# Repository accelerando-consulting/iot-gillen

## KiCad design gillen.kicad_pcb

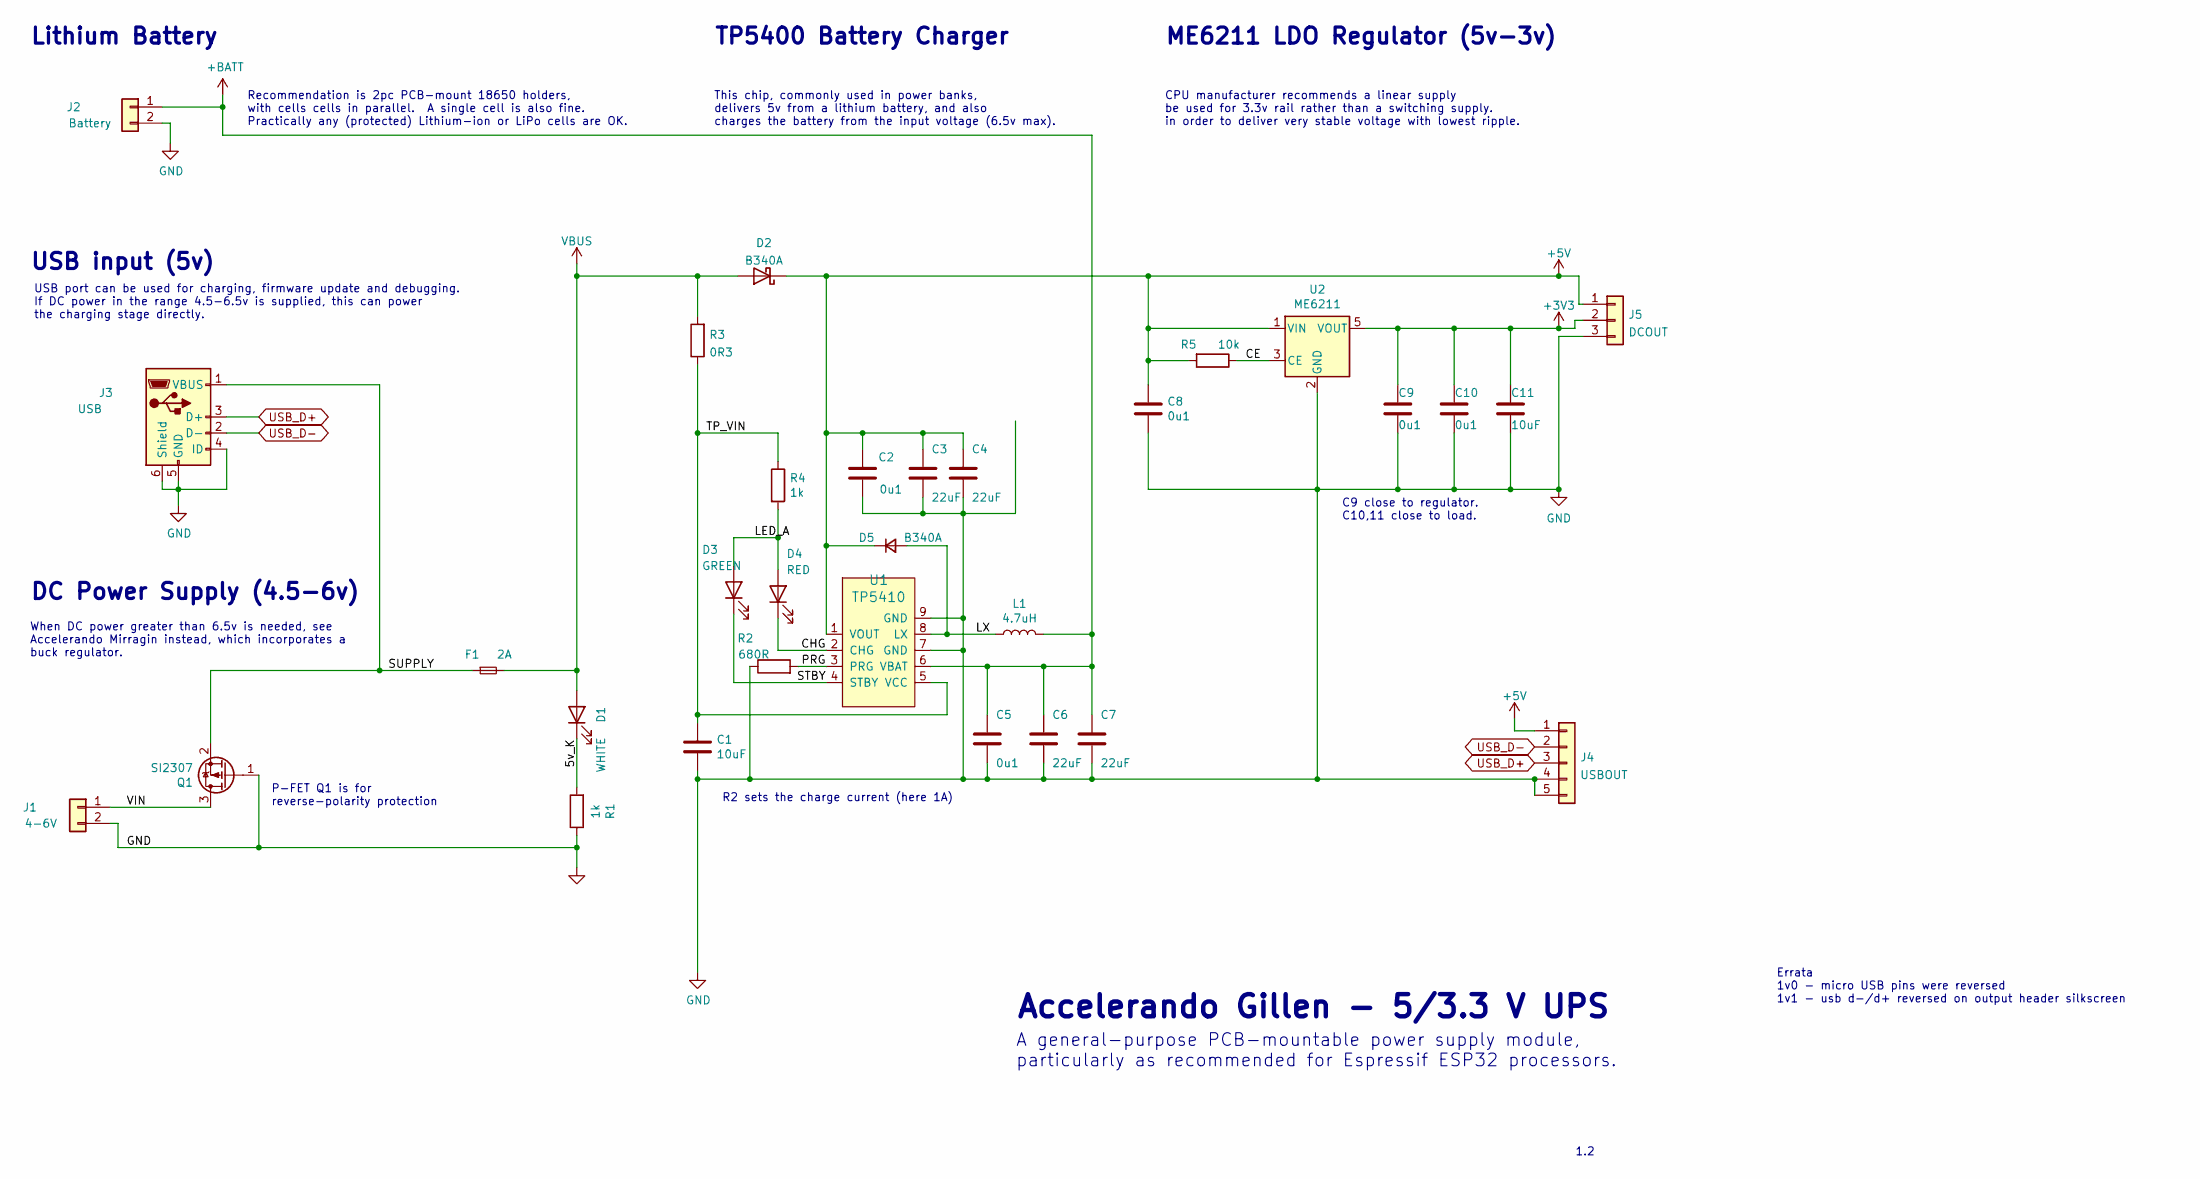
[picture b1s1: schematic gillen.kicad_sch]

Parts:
C1, C11: 10uF; C_0805_2012Metric
C2, C5, C8, C9, C10: 0u1; C_0603_1608Metric
C3, C4, C6, C7: 22uF; C_0805_2012Metric
D1: WHITE; LED_0603_1608Metric
D2: B340A; D_SMA
D3: GREEN; LED_0603_1608Metric
D4: RED; LED_0603_1608Metric
D5: B340A; D_SMB
F1: 2A; L_1206_3216Metric
J1: 4-6V; Castellated_PinHeader_1x02_P2.54mm
J2: Battery; Castellated_PinHeader_1x02_P2.54mm
J3: USB; USB_Micro_SMD
J4: USBOUT; Castellated_PinHeader_1x05_P2.54mm
J5: DCOUT; Castellated_PinHeader_1x03_P2.54mm
L1: 4.7uH; L_6.3x6.3_H3
Q1: SI2307; SOT-23
R1, R4: 1k; R_0603_1608Metric
R2: 680R; R_0603_1608Metric
R3: 0R3; R_1206_3216Metric
R5: 10k; R_0603_1608Metric
U1: TP5410; SOIC-8-1EP_3.9x4.9mm_P1.27mm_EP2.29x3mm
U2: ME6211; SOT-23-5

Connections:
+3V3: C9.1, C10.1, C11.1, J5.2, U2.5 (VOUT)
+5V: C2.2, C3.1, C4.1, C8.1, D2.1 (K), D5.1 (K), J4.1, J5.1, R5.2, U1.1 (VOUT), U2.1 (VIN)
+BATT: C5.1, C6.1, C7.1, J2.1, L1.2, U1.6 (VBAT)
/5v_K: D1.1 (K), R1.2
/CE: R5.1, U2.3 (CE)
/CHG: D4.1 (K), U1.2 (CHG)
/LED_A: D3.2 (A), D4.2 (A), R4.2
/LX: D5.2 (A), L1.1, U1.8 (LX)
/PRG: R2.2, U1.3 (PRG)
/STBY: D3.1 (K), U1.4 (STBY)
/SUPPLY: F1.1, J3.1 (VBUS), Q1.2 (S)
/TP_VIN: C1.1, R3.1, R4.1, U1.5 (VCC)
/VIN: J1.1, Q1.3 (D)
GND: C1.2, C2.1, C3.2, C4.2, C5.2, C6.2, C7.2, C8.2, C9.2, C10.2, C11.2, J1.2, J2.2, J3.4 (ID), J3.5 (GND), J3.6 (Shield), J4.4, J4.5, J5.3, Q1.1 (G), R1.1, R2.1, U1.7 (GND), U1.9 (GND), U2.2 (GND)
USB_D+: J3.3 (D+), J4.3
USB_D-: J3.2 (D-), J4.2
VBUS: D1.2 (A), D2.2 (A), F1.2, R3.2

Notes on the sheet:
R2 sets the charge current (here 1A)
DC Power Supply (4.5-6v)
USB input (5v)
USB port can be used for charging, firmware update and debugging. If DC power in the range 4.5-6.5v is supplied, this can power the charging stage directly.
P-FET Q1 is for reverse-polarity protection
CPU manufacturer recommends a linear supply be used for 3.3v rail rather than a switching supply. in order to deliver very stable voltage with lowest ripple.
TP5400 Battery Charger
When DC power greater than 6.5v is needed, see Accelerando Mirragin instead, which incorporates a buck regulator.
Lithium Battery
This chip, commonly used in power banks, delivers 5v from a lithium battery, and also charges the battery from the input voltage (6.5v max).
Recommendation is 2pc PCB-mount 18650 holders, with cells cells in parallel. A single cell is also fine. Practically any (protected) Lithium-ion or LiPo cells are OK.
Accelerando Gillen - 5/3.3 V UPS
Errata 1v0 - micro USB pins were reversed 1v1 - usb d-/d+ reversed on output header silkscreen
1.2
C9 close to regulator. C10,11 close to load.
A general-purpose PCB-mountable power supply module, particularly as recommended for Espressif ESP32 processors.
ME6211 LDO Regulator (5v-3v)

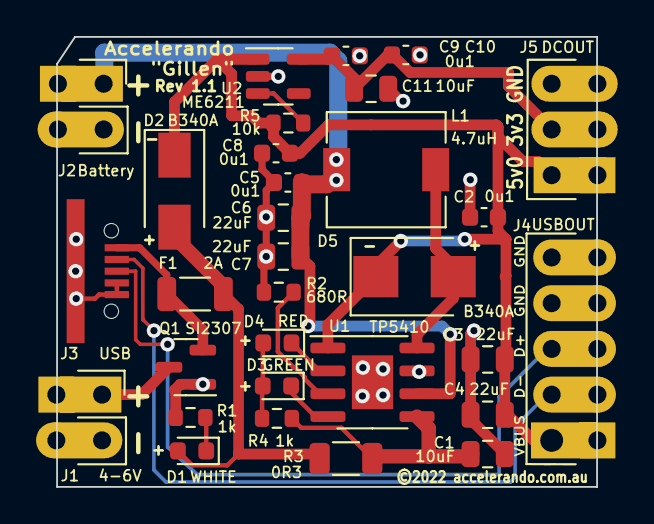
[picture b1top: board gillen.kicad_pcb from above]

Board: 2 copper layers, 30.0 x 25.0 mm, 31 parts (0 on the bottom side), 17 nets.

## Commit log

2022-07-31 Gillen v1.1 - tps5410 power supply
2024-05-21 Address DRC and tidy up assembly info

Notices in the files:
gillen.kicad_pcb:
©2022 accelerando.com.au
